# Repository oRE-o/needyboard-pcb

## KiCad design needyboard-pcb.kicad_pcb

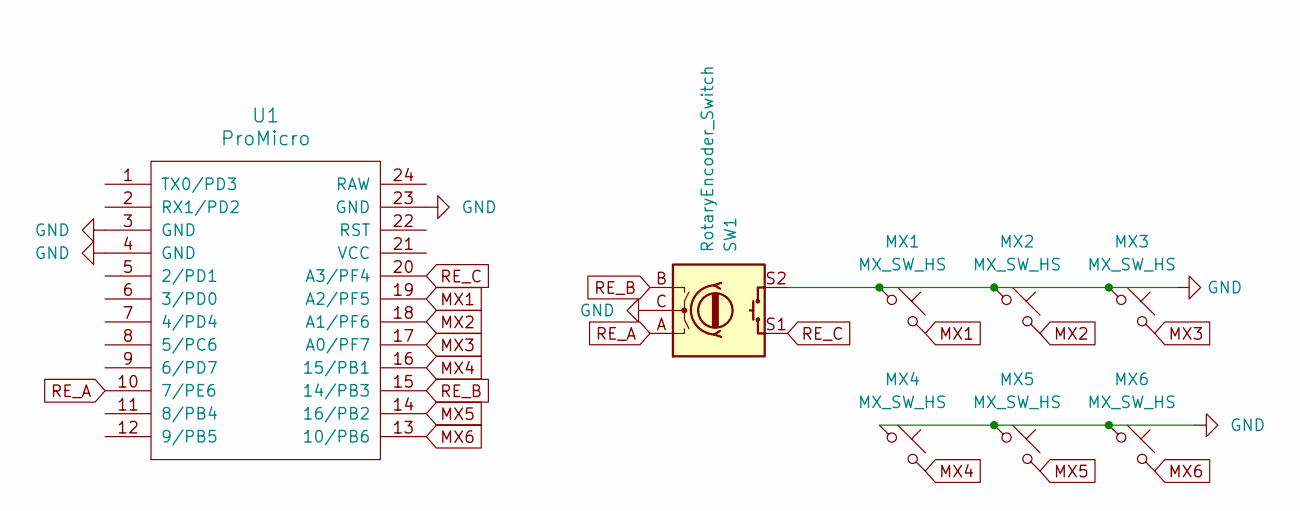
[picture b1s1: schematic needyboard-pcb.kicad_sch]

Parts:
MX1, MX2, MX3, MX4, MX5, MX6: MX_SW_HS; SW_MX_HS_1u
SW1: RotaryEncoder_Switch; RotaryEncoder_EC11
U1: ProMicro; ArduinoProMicro

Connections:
GND: MX1.1, MX2.1, MX3.1, MX4.1, MX5.1, MX6.1, SW1.C, SW1.S2, U1.3 (GND), U1.4 (GND), U1.23 (GND)
MX1: MX1.2, U1.19 (A2/PF5)
MX2: MX2.2, U1.18 (A1/PF6)
MX3: MX3.2, U1.17 (A0/PF7)
MX4: MX4.2, U1.16 (15/PB1)
MX5: MX5.2, U1.14 (16/PB2)
MX6: MX6.2, U1.13 (10/PB6)
RE_A: SW1.A, U1.10 (7/PE6)
RE_B: SW1.B, U1.15 (14/PB3)
RE_C: SW1.S1, U1.20 (A3/PF4)

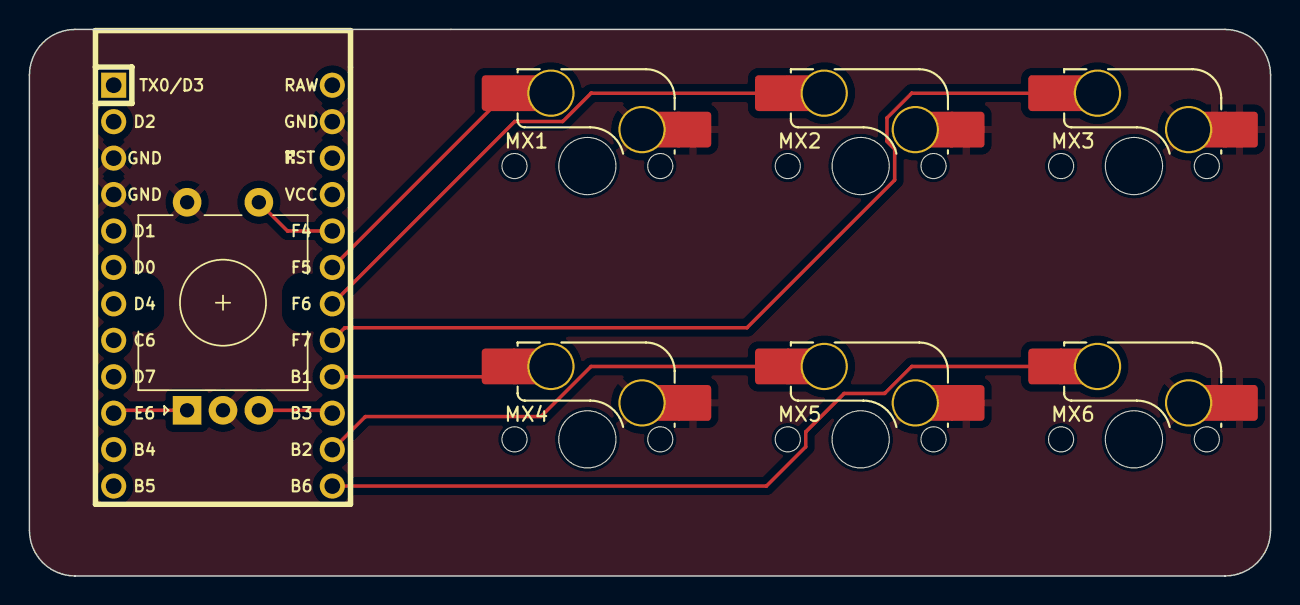
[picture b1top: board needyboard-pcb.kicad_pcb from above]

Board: 2 copper layers, 86.5 x 38.1 mm, 8 parts (0 on the bottom side), 10 nets.

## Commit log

2023-08-23 first
2023-08-23 Add Submodules
2023-08-23 add footprint lib
2023-08-24 complete
2023-08-24 reload
